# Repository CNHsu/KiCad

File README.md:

# KiCad
KiCad study database
KiCad : personal build library "mylib" zip file (unzip size over 5GB) located in dropbox cnhsu account

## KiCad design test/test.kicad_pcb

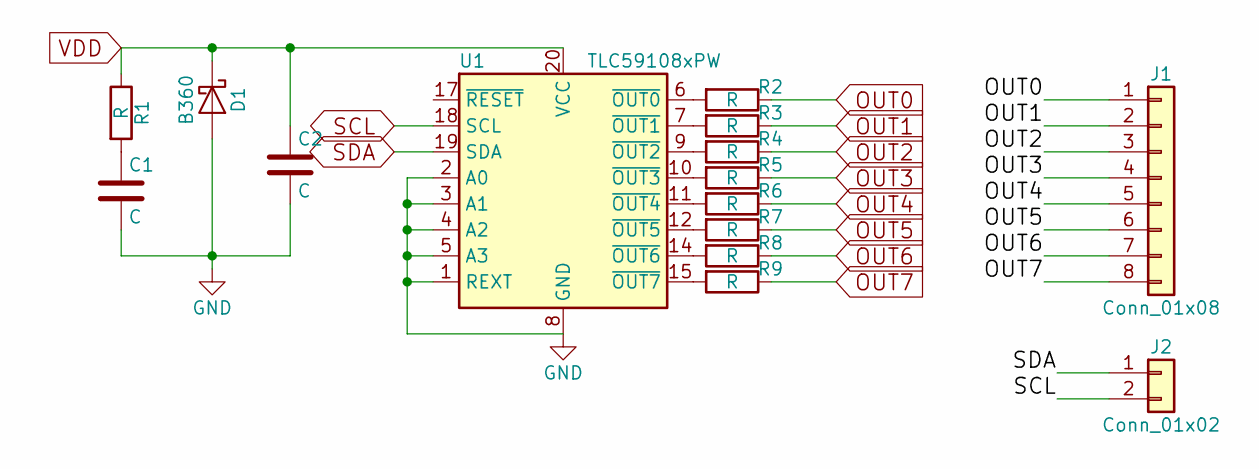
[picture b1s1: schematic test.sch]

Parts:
C1, C2: C; C_0402
D1: B360; SMC_Standard
J1: Conn_01x08; Pin_Header_Straight_1x08_Pitch1.00mm
J2: Conn_01x02; Pin_Header_Straight_1x02_Pitch1.00mm
R1, R2, R3, R4, R5, R6, R7, R8, R9: R; R_0402
U1: TLC59108xPW; ETSSOP-20-1EP_4.4x6.5mm_Pitch0.65mm

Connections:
GND: C1.2, C2.2, D1.2 (A), U1.1 (REXT), U1.2 (A0), U1.3 (A1), U1.4 (A2), U1.5 (A3), U1.8 (GND), U1.13 (GND), U1.16 (GND)
unnamed: C1.1, R1.2
unnamed: R2.2, U1.6 (~OUT0)
unnamed: R3.2, U1.7 (~OUT1)
unnamed: R4.2, U1.9 (~OUT2)
unnamed: R5.2, U1.10 (~OUT3)
unnamed: R6.2, U1.11 (~OUT4)
unnamed: R7.2, U1.12 (~OUT5)
unnamed: R8.2, U1.14 (~OUT6)
unnamed: R9.2, U1.15 (~OUT7)
OUT0: J1.1, R2.1
OUT1: J1.2, R3.1
OUT2: J1.3, R4.1
OUT3: J1.4, R5.1
OUT4: J1.5, R6.1
OUT5: J1.6, R7.1
OUT6: J1.7, R8.1
OUT7: J1.8, R9.1
SCL: J2.2, U1.18 (SCL)
SDA: J2.1, U1.19 (SDA)
VDD: C2.1, D1.1 (K), R1.1, U1.20 (VCC)

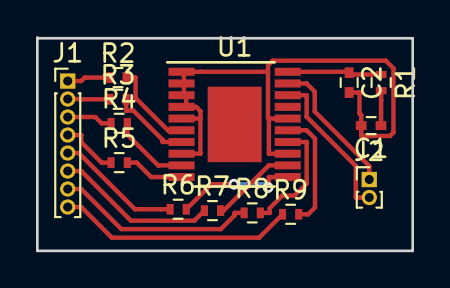
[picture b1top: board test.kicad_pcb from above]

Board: 2 copper layers, 20.9 x 11.9 mm, 14 parts (0 on the bottom side), 21 nets.

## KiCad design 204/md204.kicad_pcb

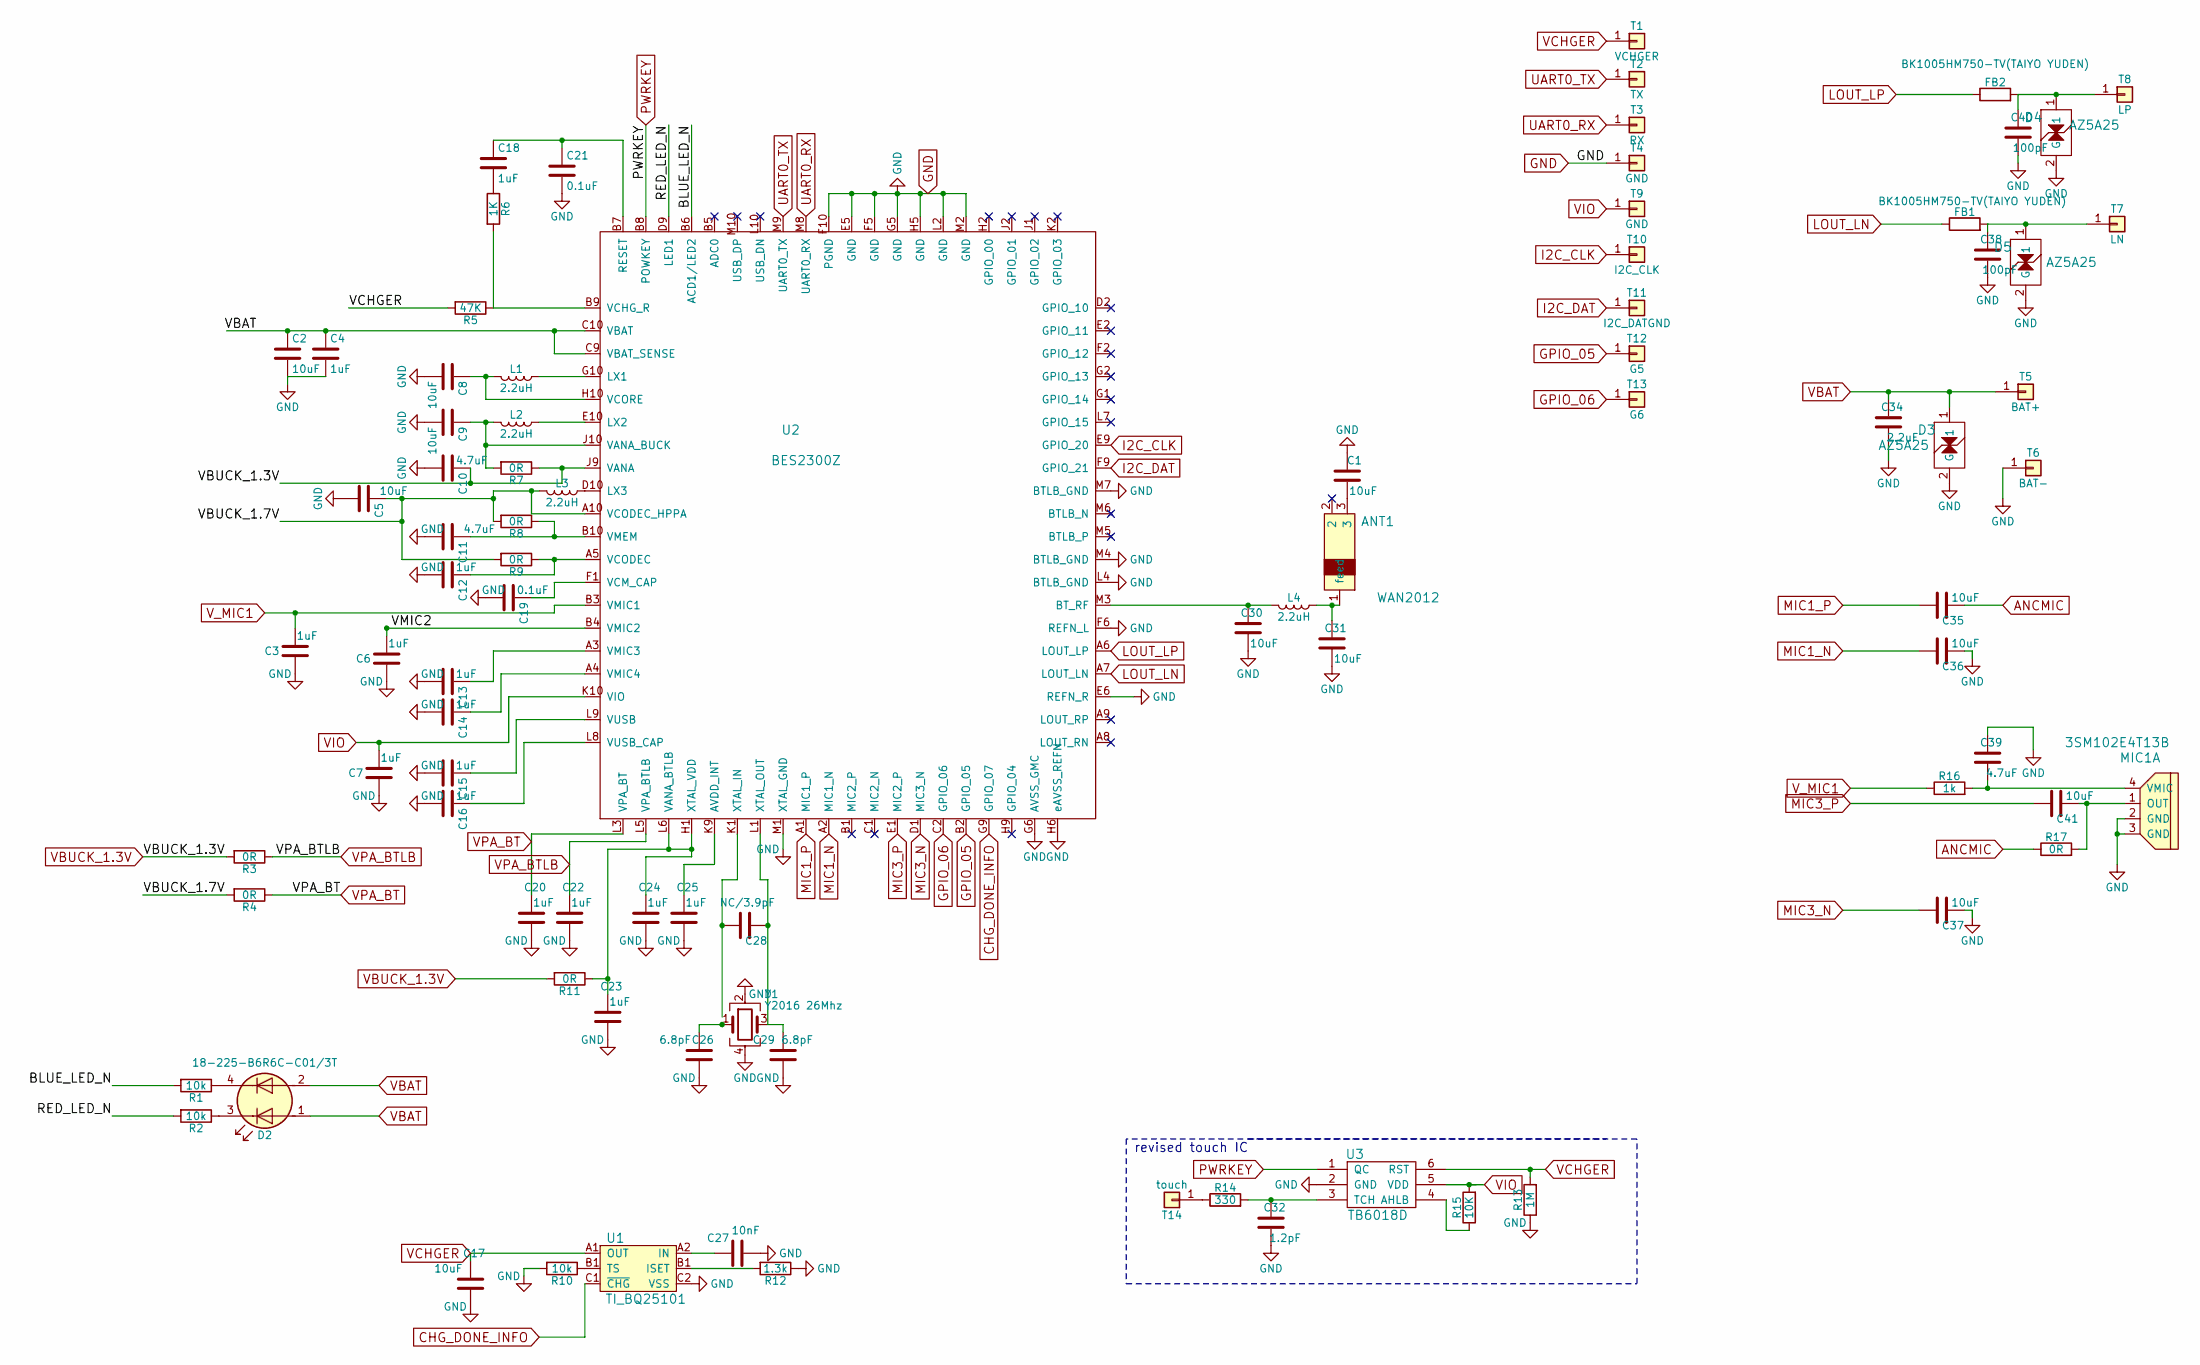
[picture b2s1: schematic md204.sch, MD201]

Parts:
ANT1: WAN2012
C1, C2, C5, C8, C9, C30, C31, C35, C36, C37, C41: 10uF; C_0402
C3, C4, C6, C7, C12, C13, C14, C15, C16, C18, C20, C22, C23, C24, C25: 1uF; C_0201
C10, C11, C39: 4.7uF; C_0402
C17: 10uF; C_0401
C19, C21: 0.1uF; C_0201
C26, C29: 6.8pF; C_0201
C27: 10nF; C_0201
C28: NC/3.9pF; C_0201
C32: 1.2pF; C_0402
C34: 2.2uF; C_0201
C38, C40: 100pF; C_0201
D2: 18-225-B6R6C-C01/3T; Y2016_SOT-883
D3, D4, D5: AZ5A25; D_0603
FB1, FB2: BK1005HM750-TV(TAIYO YUDEN); BK1005HM750-T
L1, L2, L3, L4: 2.2uH; C_0402
MIC1: 3SM102E4T13B; 3S_MIC
R1, R2, R10: 10k; R_0201
R3, R4, R7, R8, R9, R11: 0R; R_0201
R5: 47K; R_0201
R6: 1K; R_0201
R12: 1.3k; R_0201
R13: 1M; R_0201
R14: 330; R_0201
R15: 10K; R_0201
R16: 1k; R_0201
R17: 0R; R_0402
T1: VCHGER; pad_1x1mm
T2: TX; pad_1x1mm
T3: RX; pad_1x1mm
T4, T9: GND; pad_1x1mm
T5: BAT+; pad_1x1mm
T6: BAT-; pad_1x1mm
T7: LN; pad_1x1mm
T8: LP; pad_1x1mm
T10: I2C_CLK; pad_1x1mm
T11: I2C_DATGND; pad_1x1mm
T12: G5; pad_1x1mm
T13: G6; pad_1x1mm
T14: touch; pad_1x1mm
U1: TI_BQ25101; Texas_DSBGA-6_2x3_0.9x1.4mm(2)
U2: BES2300Z; BES(2) BGA-80_6.2x4.5x1.3
U3: TB6018D; DFN-6-1EP_2x2mm_Pitch0.65mm
Y1: Y2016 26Mhz; Y2016_SOT-883

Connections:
/BLUE_LED_N: R1.2, U2.B6 (ACD1/LED2)
/RED_LED_N: R2.2, U2.D9 (LED1)
/VBUCK_1.7V: C5.1, L3.2, R4.2, R8.2, R9.2, U2.A10 (VCODEC_HPPA)
/VMIC2: C6.2, U2.B4 (VMIC2)
ANCMIC: C35.2, R17.1
CHG_DONE_INFO: U1.C1 (~CHG), U2.G9 (GPIO_07)
GND: C1.2, C2.2, C3.1, C4.2, C5.2, C6.1, C7.1, C8.2, C9.2, C10.2, C11.2, C12.2, C13.2, C14.2, C15.2, C16.2, C17.1, C19.2, C20.1, C21.2, C22.1, C23.1, C24.1, C25.1, C26.1, C27.2, C29.1, C30.1, C31.1, C32.1, C34.1, C36.2, C37.2, C38.1, C39.2, C40.1, D3.2 (G), D4.2 (G), D5.2 (G), MIC1.2 (GND), MIC1.3 (GND), R10.2, R12.1, R13.1, T4.1, T6.1, U1.C2 (VSS), U2.E5 (GND), U2.E6 (REFN_R), U2.F5 (GND), U2.F6 (REFN_L), U2.F10 (PGND), U2.G5 (GND), U2.G6 (AVSS_GMC), U2.H5 (GND), U2.H6 (eAVSS_REFN), U2.L2 (GND), U2.L4 (BTLB_GND), U2.M1 (XTAL_GND), U2.M2 (GND), U2.M4 (BTLB_GND), U2.M7 (BTLB_GND), U3.2 (GND), Y1.2, Y1.4
GPIO_05: T12.1, U2.B2 (GPIO_05)
GPIO_06: T13.1, U2.C2 (GPIO_06)
I2C_CLK: T10.1, U2.E9 (GPIO_20)
I2C_DAT: T11.1, U2.F9 (GPIO_21)
LOUT_LN: FB1.1, U2.A7 (LOUT_LN)
LOUT_LP: FB2.1, U2.A6 (LOUT_LP)
MIC1_N: C36.1, U2.A2 (MIC1_N)
MIC1_P: C35.1, U2.A1 (MIC1_P)
MIC3_N: C37.1, U2.D1 (MIC3_N)
MIC3_P: C41.1, U2.E1 (MIC2_P)
unnamed: ANT1.1 (feed), C31.2, L4.1
unnamed: ANT1.3, C1.1
unnamed: C8.1, L1.2, U2.H10 (VCORE)
unnamed: C9.1, L2.2, R7.2, U2.J10 (VANA_BUCK)
unnamed: C11.1, R8.1, U2.B10 (VMEM)
unnamed: C12.1, R9.1, U2.A5 (VCODEC)
unnamed: C13.1, U2.A3 (VMIC3)
unnamed: C14.1, U2.A4 (VMIC4)
unnamed: C15.1, U2.L9 (VUSB)
unnamed: C16.1, U2.L8 (VUSB_CAP)
unnamed: C18.1, C21.1, U2.B7 (RESET)
unnamed: C18.2, R6.1
unnamed: C19.1, U2.F1 (VCM_CAP)
unnamed: C23.2, C24.2, R11.1, U2.H1 (XTAL_VDD), U2.L6 (VANA_BTLB)
unnamed: C25.2, U2.K9 (AVDD_INT)
unnamed: C26.2, Y1.1
unnamed: C27.1, U1.A2 (IN)
unnamed: C28.1, U2.K1 (XTAL_IN)
unnamed: C28.2, C29.2, U2.L1 (XTAL_OUT), Y1.3
unnamed: C30.2, L4.2, U2.M3 (BT_RF)
unnamed: C32.2, R14.2, U3.3 (TCH)
unnamed: C38.2, D5.1, FB1.2, T7.1
unnamed: C39.1, MIC1.4 (VMIC), R16.2
unnamed: C40.2, D4.1, FB2.2, T8.1
unnamed: C41.2, MIC1.1 (OUT), R17.2
unnamed: D2.3 (K1), R2.1
unnamed: D2.4 (K2), R1.1
unnamed: L1.1, U2.G10 (LX1)
unnamed: L2.1, U2.E10 (LX2)
unnamed: L3.1, U2.D10 (LX3)
unnamed: R5.1, R6.2, U2.B9 (VCHG_R)
unnamed: R14.1, T14.1
unnamed: R15.1, U3.4 (AHLB)
PWRKEY: U2.B8 (POWKEY), U3.1 (QC)
UART0_RX: T3.1, U2.M8 (UART0_RX)
UART0_TX: T2.1, U2.M9 (UART0_TX)
VBAT: C2.1, C4.1, C34.2, D2.1 (A1), D2.2 (A2), D3.1, T5.1, U2.C9 (VBAT_SENSE), U2.C10 (VBAT)
VBUCK_1.3V: C10.1, R3.2, R7.1, R11.2, U2.J9 (VANA)
VCHGER: C17.2, R5.2, R13.2, T1.1, U1.A1 (OUT), U3.6 (RST)
VIO: C7.2, R15.2, T9.1, U2.K10 (VIO), U3.5 (VDD)
VPA_BT: C20.2, R4.1, U2.L3 (VPA_BT)
VPA_BTLB: C22.2, R3.1, U2.L5 (VPA_BTLB)
V_MIC1: C3.2, R16.1, U2.B3 (VMIC1)

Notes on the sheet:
revised touch IC

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
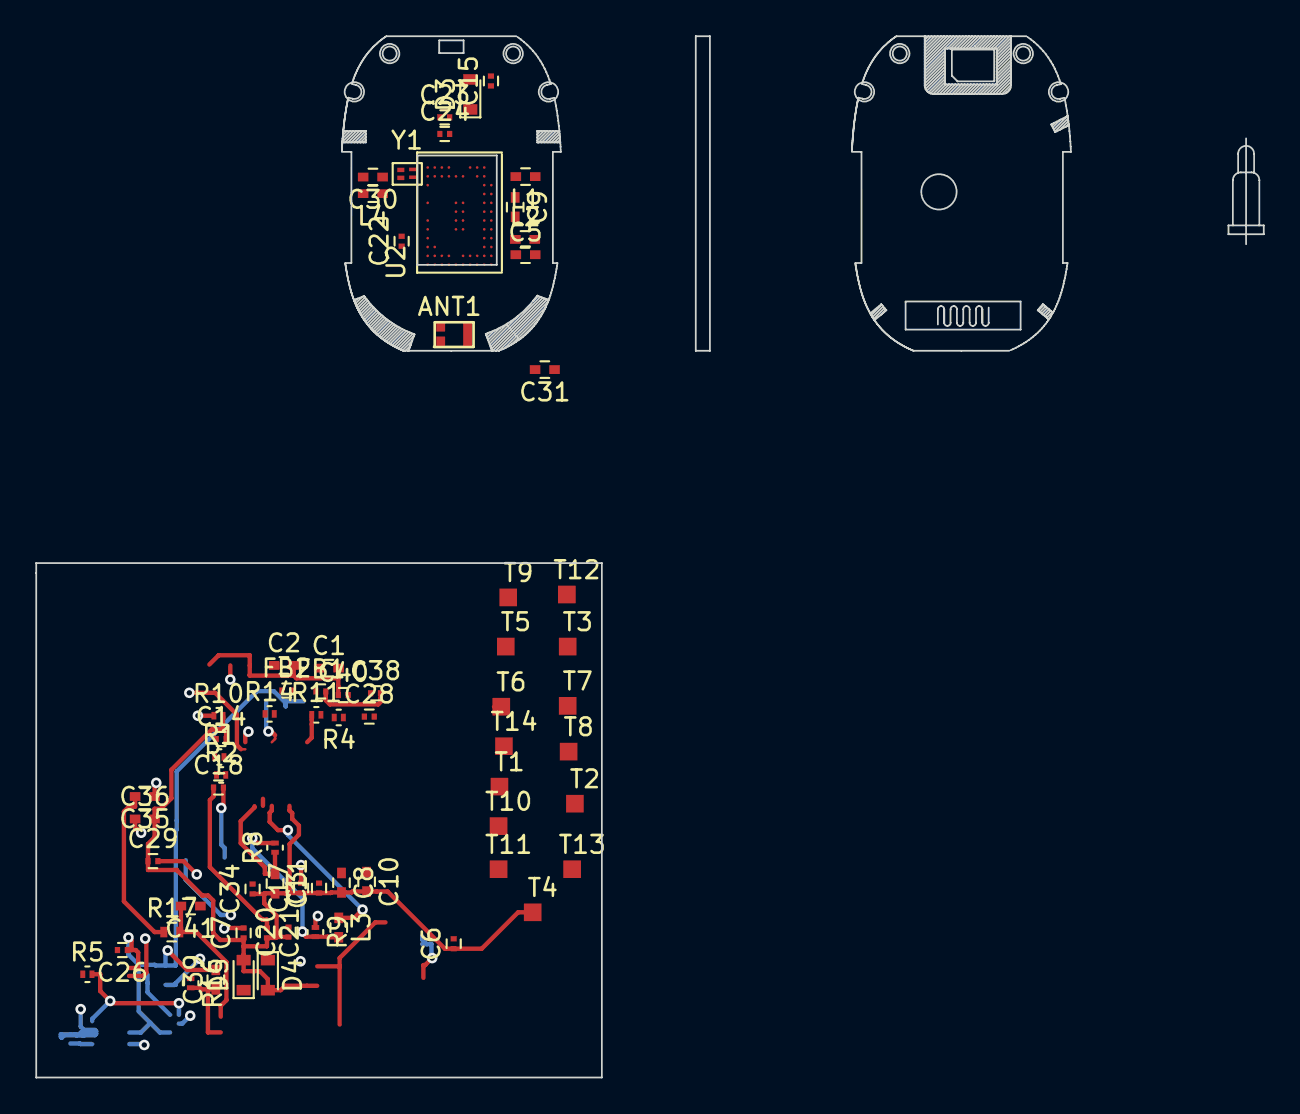
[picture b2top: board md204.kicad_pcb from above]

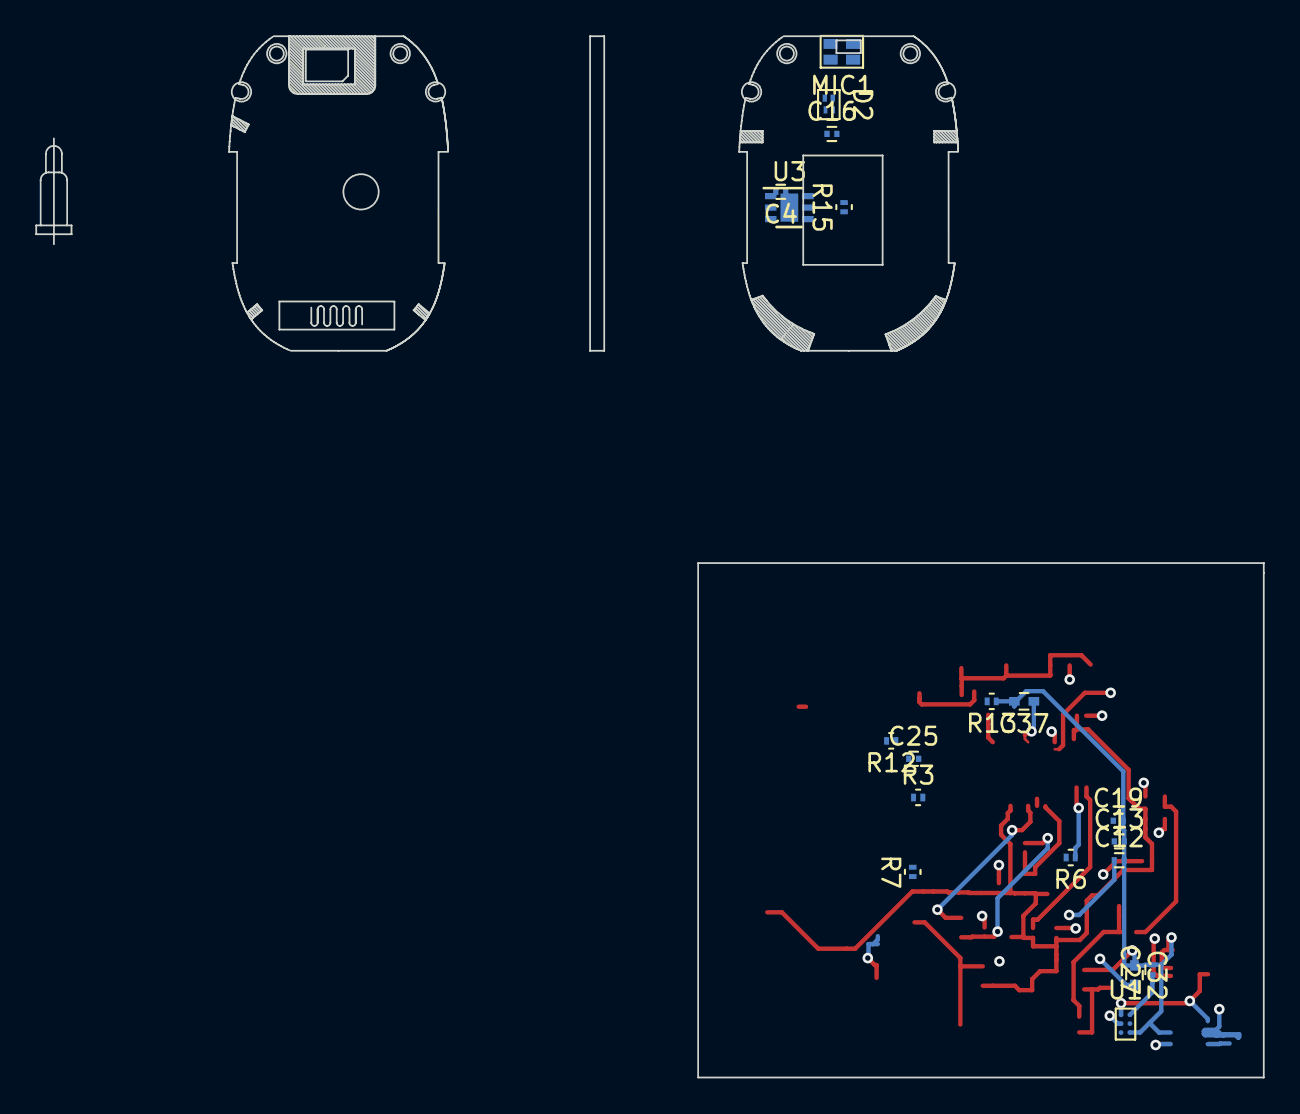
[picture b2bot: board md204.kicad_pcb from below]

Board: 4 copper layers, 69.5 x 58.9 mm, 87 parts (19 on the bottom side), 61 nets.
